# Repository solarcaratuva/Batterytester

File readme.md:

# UVA Solar Car Battery Assessment and Testing Device
## [Protected under Creative Commons Attribution ShareAlike CC BY-SA 4.0](https://creativecommons.org/licenses/by-sa/4.0/legalcode)

### This project was developed by the UVa Solar Car Team in order to test large numbers of lithium ion 18650 cells. By testing ESR and capacity one can be confident that each and every cell tested performs as expected and no cells have arrived DOA. Individually characterizing and 'binning' each cell allows us to arrange the cells in the final battery bank such that each module will have as close to identical capacity, reducing the chance of the modules SoC from drifting significantly over charge/discharge cycles.

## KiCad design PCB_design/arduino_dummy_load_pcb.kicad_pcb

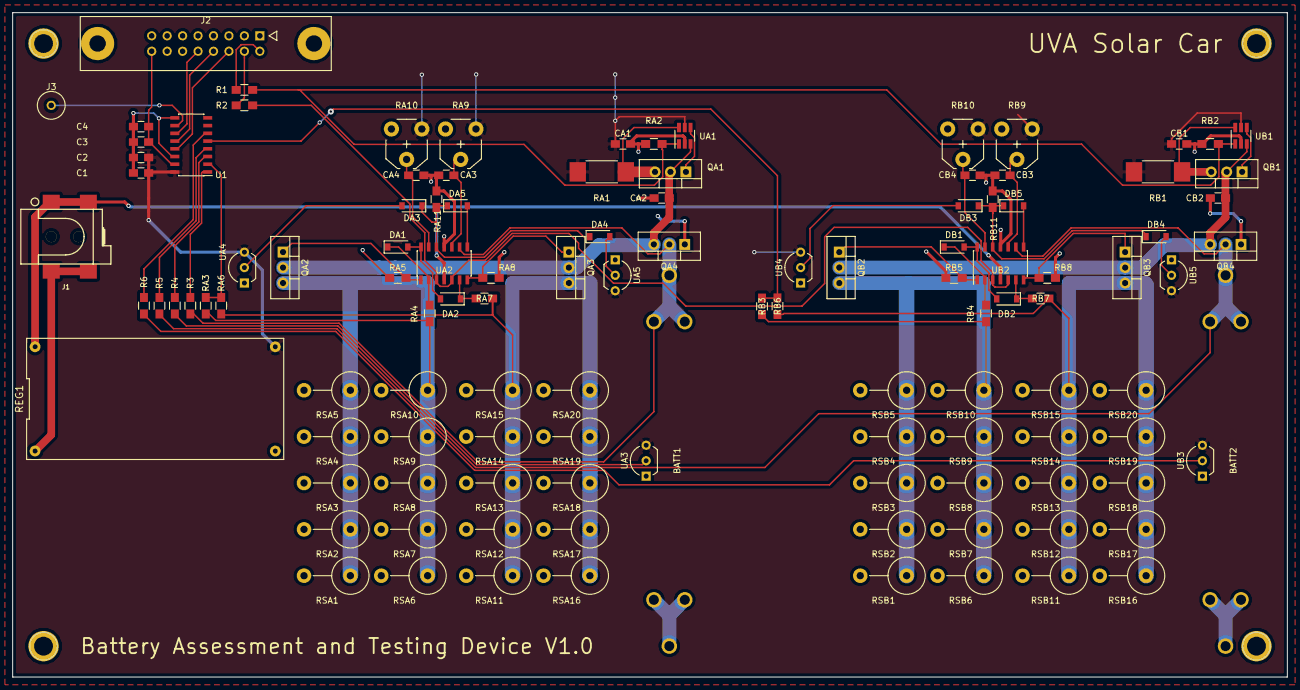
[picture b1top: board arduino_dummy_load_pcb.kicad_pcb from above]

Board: 2 copper layers, 209.6 x 109.2 mm, 115 parts (0 on the bottom side), 55 nets.

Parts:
BATT1, BATT2: Battery_Cell; 18650
C1, C3: 10uF; C_0805_HandSoldering
C2, C4: 100nF; C_0805_HandSoldering
CA1, CA2: 10uF; C_0805_HandSoldering
CA3, CA4: 100nF; C_0805_HandSoldering
CB1, CB2: 10uF; C_0805_HandSoldering
CB3, CB4: 100nF; C_0805_HandSoldering
DA1, DA2, DA3, DA4, DA5: D; D_SOD-123
DB1, DB2, DB3, DB4, DB5: D; D_SOD-123
J1: Barrel_Jack; CUI-PJ-002AH-SMT_dc-barrel-jack
J2: Conn_02x08_Odd_Even; he10-16d
J3: Conn_01x01; 1pin
QA1, QA4: IPP45P03P4L-11; TO-220-3_Vertical
QA2, QA3: IRFZ44N; TO-220-3_Vertical
QB1, QB4: IPP45P03P4L-11; TO-220-3_Vertical
QB2, QB3: IRFZ44N; TO-220-3_Vertical
R1, R2, R3, R4, R5, R6: 47k; R_0805_HandSoldering
RA1: 50m; R_2512_HandSoldering
RA2, RA3, RA4, RA5, RA6, RA7, RA8: 47k; R_0805_HandSoldering
RA9, RA10: POT; Potentiometer_Trimmer_VishaySpectrol_Econtrim-Type36M
RA11: 10k; R_0805_HandSoldering
RB1: 50m; R_2512_HandSoldering
RB2, RB3, RB4, RB5, RB6, RB7, RB8: 47k; R_0805_HandSoldering
RB9, RB10: POT; Potentiometer_Trimmer_VishaySpectrol_Econtrim-Type36M
RB11: 10k; R_0805_HandSoldering
REG1: REG; LM2596_module
RSA1, RSA2, RSA3, RSA4, RSA5, RSA6, RSA7, RSA8, RSA9, RSA10, RSA11, RSA12, RSA13, RSA14, RSA15, RSA16, RSA17, RSA18, RSA19, RSA20: 10; R_Axial_DIN0617_L17.0mm_D6.0mm_P7.62mm_Vertical
RSB1, RSB2, RSB3, RSB4, RSB5, RSB6, RSB7, RSB8, RSB9, RSB10, RSB11, RSB12, RSB13, RSB14, RSB15, RSB16, RSB17, RSB18, RSB19, RSB20: 10; R_Axial_DIN0617_L17.0mm_D6.0mm_P7.62mm_Vertical
U1: MCP3208; SOIC-16_3.9x9.9mm_Pitch1.27mm
UA1: MCP73826; SOT-23-6_Handsoldering
UA2: LM324; SOIC-14_3.9x8.7mm_Pitch1.27mm
UA3, UA4, UA5: TMP36; TO-92_Inline_Wide
UB1: MCP73826; SOT-23-6_Handsoldering
UB2: LM324; SOIC-14_3.9x8.7mm_Pitch1.27mm
UB3, UB4, UB5: TMP36; TO-92_Inline_Wide

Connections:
+5V: C1.1, C2.1, CA1.1, CB1.1, RA1.1, RA9.1, RA10.1, RB1.1, RB9.1, RB10.1, REG1.4, U1.16, UA1.5, UA3.3, UA4.3, UA5.3, UB1.5, UB3.3, UB4.3, UB5.3
+9V: J1.1, REG1.1, UA2.4, UB2.4
/TEST-UNIT-A/STOP: DA1.2, DA2.2, UA2.14
/TEST-UNIT-B/STOP: DB1.2, DB2.2, UB2.14
BATT_A: BATT1.1, QA4.2, R3.2, UA2.9
BATT_B: BATT2.1, QB4.2, R5.2, UB2.9
CELL_TEMP_A: R4.2, UA3.2
CELL_TEMP_B: R6.2, UB3.2
CHARGE: R1.2, RA2.1, RB2.1, UA1.1, UB1.1
GND: BATT1.2, BATT2.2, C1.2, C2.2, C3.1, C4.1, CA1.2, CA2.2, CA3.2, CA4.2, CB1.2, CB2.2, CB3.2, CB4.2, J2.1, J2.3, J2.5, J2.7, J2.9, J2.11, J2.13, J2.15, QA4.1, QB4.1, RA2.2, RA5.1, RA8.1, RA9.3, RA10.3, RA11.1, RB2.2, RB5.1, RB8.1, RB9.3, RB10.3, RB11.1, REG1.3, RSA1.2, RSA2.2, RSA3.2, RSA4.2, RSA5.2, RSA6.2, RSA7.2, RSA8.2, RSA9.2, RSA10.2, RSA11.2, RSA12.2, RSA13.2, RSA14.2, RSA15.2, RSA16.2, RSA17.2, RSA18.2, RSA19.2, RSA20.2, RSB1.2, RSB2.2, RSB3.2, RSB4.2, RSB5.2, RSB6.2, RSB7.2, RSB8.2, RSB9.2, RSB10.2, RSB11.2, RSB12.2, RSB13.2, RSB14.2, RSB15.2, RSB16.2, RSB17.2, RSB18.2, RSB19.2, RSB20.2, U1.9, U1.14, UA1.2, UA2.11, UA3.1, UA4.1, UA5.1, UB1.2, UB2.11, UB3.1, UB4.1, UB5.1
I_OUT_A: RA3.1, RA6.1, U1.2
I_OUT_B: RB3.1, RB6.1, U1.5
I_SET: R2.2, UA2.3, UA2.5, UB2.3, UB2.5
unnamed: CA2.1, QA1.2, QA2.2, QA3.2, QA4.3, UA1.3
unnamed: CA3.1, RA9.2, UA2.10
unnamed: CA4.1, RA10.2, UA2.13
unnamed: CB2.1, QB1.2, QB2.2, QB3.2, QB4.3, UB1.3
unnamed: CB3.1, RB9.2, UB2.10
unnamed: CB4.1, RB10.2, UB2.13
unnamed: DA1.1, RA4.2, UA2.2
unnamed: DA2.1, RA7.2, UA2.6
unnamed: DA3.1, DA4.1, DA5.1, RA11.2, UA2.12
unnamed: DA3.2, UA4.2
unnamed: DA4.2, UA5.2
unnamed: DA5.2, UA2.8
unnamed: DB1.1, RB4.2, UB2.2
unnamed: DB2.1, RB7.2, UB2.6
unnamed: DB3.1, DB4.1, DB5.1, RB11.2, UB2.12
unnamed: DB3.2, UB4.2
unnamed: DB4.2, UB5.2
unnamed: DB5.2, UB2.8
unnamed: J1.2, J1.3, REG1.2
unnamed: J2.2, R1.1
unnamed: J2.4, R2.1
unnamed: J2.6, U1.13
unnamed: J2.8, U1.12
unnamed: J2.10, U1.11
unnamed: J3.1, U1.10
unnamed: QA1.1, UA1.4
unnamed: QA1.3, RA1.2, UA1.6
unnamed: QA2.1, RA5.2, UA2.1
unnamed: QA2.3, RA3.2, RA4.1, RSA1.1, RSA2.1, RSA3.1, RSA4.1, RSA5.1, RSA6.1, RSA7.1, RSA8.1, RSA9.1, RSA10.1
unnamed: QA3.1, RA8.2, UA2.7
unnamed: QA3.3, RA6.2, RA7.1, RSA11.1, RSA12.1, RSA13.1, RSA14.1, RSA15.1, RSA16.1, RSA17.1, RSA18.1, RSA19.1, RSA20.1
unnamed: QB1.1, UB1.4
unnamed: QB1.3, RB1.2, UB1.6
unnamed: QB2.1, RB5.2, UB2.1
unnamed: QB2.3, RB3.2, RB4.1, RSB1.1, RSB2.1, RSB3.1, RSB4.1, RSB5.1, RSB6.1, RSB7.1, RSB8.1, RSB9.1, RSB10.1
unnamed: QB3.1, RB8.2, UB2.7
unnamed: QB3.3, RB6.2, RB7.1, RSB11.1, RSB12.1, RSB13.1, RSB14.1, RSB15.1, RSB16.1, RSB17.1, RSB18.1, RSB19.1, RSB20.1
unnamed: R3.1, U1.1
unnamed: R4.1, U1.3
unnamed: R5.1, U1.4
unnamed: R6.1, U1.6
VREF: C3.2, C4.2, J2.16, U1.15

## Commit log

2017-10-24 Initial commit of BatteryTester code. It's just messing with some registers to setup fast PWM. Lots of work ahead of us!
2017-10-25 Initial circuit design (concept)x
2017-10-25 Created protection circuitry for channel B, added decoupling capacitor for 78L05, rearranged a few elements
2017-10-26 Added lithium ion charging circuitry and labeled all components
2017-10-26 Fixed connector. This should be the first version of the schematic which is fully functional, but completly untested.
2017-10-26 Fixed a few "bugs" (forgot to do DRC check!) and also added the batteries!
2017-10-26 Gave components footprints and started PCB layout
2017-10-28 added gitignore
2017-10-29 Latest commit
2017-11-04 Fixed a few mistakes, Implemented reverse polarity protection w/ MOSFETs.
2017-11-09 refactored the redundant battery testing units into hierarchical blocks. TODO: still need to add voltage reference component and create custom PCB footprint for the battery.
2017-11-12 stuff.
2017-11-18 KiCad routing for the win!
2017-11-18 Adding a test file
2017-11-18 Added Data_Logging.m
2017-11-18 Add files via upload
    RTC Clock and SD Card Combined Code. Currently reads in RTC hour/minute/second and writes it to a unique filename. The unique filename consists of: battery number (pin 4 or 5), batch number (batch 1 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
2017-11-18 added discharge code and .h file for MCP3208
2017-11-22 changes have been made. Lives have been improved. I'm not the poetic type but this just worked. :)
2017-11-22 I placed all of the arduino files into one common directory
2017-11-25 nearly finished PCB layout and routing
2017-11-26 Finalized/finished PCB layout. Phew! Version 0.00. Hopefully it works (fingers crossed)!
2017-11-27 adding gerber files
2017-11-27 added drill file
2017-12-03 Resized vias in order to reduce potential showstoppers in DFM Checks
2017-12-04 PCB with only one DFM error
2017-12-04 Cleaned up export folder
2017-12-05 Fixed apparent Kicad DRC errors (VCC floodfill in some areas was isolated from VCC.) and one via that was too close to a track, and deleted some garbage traces
2017-12-05 added readme (needs lots of work), basically final PCB
2017-12-05 Added Silkscreen Labels :)
2017-12-05 Moved components in the top left away from the corner...still need to adjust copper pours
2017-12-05 Updated Gerber exports to V1.01
2017-12-05 Removed text on copper Bottom
2017-12-05 Re-routed traces that were broken by moving components away from corner
2017-12-05 Updated to Gerber Export V1.02
2017-12-05 Added mounting holes & rerouted accordingly
2017-12-05 Fixed a couple of typos
2017-12-06 Added Gerber Export V1.03
2017-12-06 Fixed the CS pin
2017-12-06 Updated to Gerber Export V1.04
2017-12-19 adding to unstable branch
2017-12-19 fixed all of @malcolms problems :)
2017-12-19 Updated to Gerber Export v1.05
2017-12-19 Added Gerber Export v1.05
2018-01-18 Moved Arduino Files into folders so that they can be easily opened
2018-01-18 Fixing directories for Arduino files
2018-01-18 moved Data_Logging.m out of Firmware directory
2018-01-18 readded Data_Logging.m
2018-01-27 Attempting to put all the code files into the same repository.
2018-01-27 Moving the files into their own Sketch Folders
2018-01-27 DischargeTypo Fixed
2018-01-27 Cleaning up the Repository
2018-01-30 removed extraneous Discharge.ino file
2018-01-30 Add SD Card test code
2018-02-01 Added functionality to SD_Card_test.ino
2018-02-01 Cleaned up data processing files
2018-02-01 Moved 'Data Logging' out of firmware and renamed it 'Data Processing'
2018-02-01 Removed extraneous Data_Loggin.m file
2018-02-01 Removed ANOTHER extraneous Data_Logging.m file
2018-02-01 Moved workshop code to new directory to organize firmware folder
2018-02-01 Removed outdated code
2018-02-01 Moved Discharge folder up a directory and deleted Tester_Code directory
2018-02-01 Renamed & reloacated SD_Card directory to Firmware/DataLogging
2018-02-01 Reorganized datalogging firmware by writing CSVWriter library
2018-02-01 Added Deke's MATLAB code for creating battery pack (thx deke)
2018-02-01 Updated broken filename in Capacities to Battery Pack script
2018-02-01 Moved old Discharge firmware to Firmware/OLD_Discharge
2018-02-01 Added files for meeting
2018-02-01 Discharger Code
    Created the Discharger class (header, class cpp, and main cpp files). Comments in the header file :D
2018-02-01 Added Jame's temperature reading software
2018-02-01 Added Header Names
2018-02-02 removed LCD software from TemperatureReading
2018-02-03 adding file readers
2018-02-03 adding file adders
2018-02-03 file readers
2018-02-03 Added Battery Identification
    Created battery identification, batteries will be numbered 1 to 416, and this can be accessed through the 'pack' matrix which contains the ordering of the batteries, and the 'pack2' matrix which cont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
2018-02-03 more edits
2018-02-03 Updated Battery Indices
    Battery Indices are now correlated to A1-A36,B1-B36...M1-M36 in a matrix called indexCells. The actual battery values are in a matrix called pack.
2018-02-04 Updated calculations in temperature sensor (Thanks James)
2018-02-04 Added lasted version of the assembly guide
2018-02-08 Battery Tester Combined Class
    Combined the Discharger and CSVWriter classes into one master arduino program to test the batteries. This arduino file will be turned into its own class.
2018-02-09 added dummy data producing file
2018-02-09 Battery Pack Working 99%
    The indexCells vector shows which batteries to place in what arrangement. The pack matrix has the voltage readings of the configured batteries. Just need to update the caps vector with actual data.
2018-02-09 Made several modifications to clean up the code base
2018-02-15 refactored some stuff and added instructions for what needs to be done.
2018-02-16 Library For Our MCP4822 DAC
    Included the MCPDAC library and some code that implements it
2018-02-16 Removed OLD_Discharge folder
2018-02-16 Updated discharge library (Thanks James & Josie)
2018-02-16 Data_Processing & Capacities_Battery ARE DONE!!!!
    THEY ARE ALL DONE!!!!! Data_Processing should be in the same folder as BatchA,BatchB,....BatchN.csv . Then, run that program. Then, go to Capacities_Battery and run that. Yay, you have finished the t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
2018-02-16 Added Source of Library
2018-02-16 Minor changes
    Minor changes
2018-02-16 Updated CSVWriter to properly format first row
2018-02-19 Added Configure_RTC (s/o to Adam) and fixed typo in TempReading
2018-02-22 Added comment about I_Set in DAC code
2018-02-22 Added RTC Library and updated #define statement so that the library doesn't need to be manually downloaded and added
2018-02-22 Removed unused define statement so that code compiles for everyone regardless of whether or not they have the MPC3208 library
2018-02-23 updated batterytester code
    Code to check temperature threshold
2018-02-23 major code cleanup
2018-02-23 Updated misc.h with more accurate comments and removed unused functions
2018-02-23 Refactored some more...updated BatteryCell library and autoindented all files
2018-02-24 Updated comment for baud rate and removed print statement from loop()
2018-02-25 added logic for writing to csv based on interrupt in newBatteryTester.ino
2018-02-28 cleaned stuff up, implemented Discharger class the way it was supposed to be implemented, and fixed problems with mcp3208. Discharger still needs some work, especally in order to use I2C later. I wou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
2018-03-08 Fixed bug with attachInterrupt. (I had to wrap the variable increment inside of a lambda since funny things happen if you don't.
2018-03-08 BatteryCell library is not useful library since it's functionallity can be replaced entirely with a simple array. Rm'ed. Added DAC functionallity to newBatteryTester and verified functionallity. Once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
    TOD
2018-03-16 stufff
2018-03-16 Updated comments for RTC config
2018-03-25 fixed bugs associated with switch found bugs with discharger.h possible bugs with decoder.h
    | |
    \ \___/ /
    \ / \ /
    ----| |-----
    / \___/ \
    / \
2018-03-26 forgot to save
2018-04-01 * implemented low voltage cutoff
2018-04-06 Fixed bugs with decoder.h Refactored NewBatteryTester folder into BatteryTester. (there is no reason to keep it anymore. It is obsolete. (Keep in mind, if anything useful was in it, it should still e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
2018-04-13 fixed tempurature reading fixed discharger naming convention fixed name for project
2018-04-13 more bug fixes (probably) me+malcolm at nite (12am)
2018-04-19 fixed a few bugs, found another that needs to be fixed: when overcurrent on a cell is detected, it needs to shut off all cells and go to the "off" state rather than read the next battery voltage, see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
2018-04-20 It's confirmed working with 8 cells simultaneously! Updated code to remove print statements
